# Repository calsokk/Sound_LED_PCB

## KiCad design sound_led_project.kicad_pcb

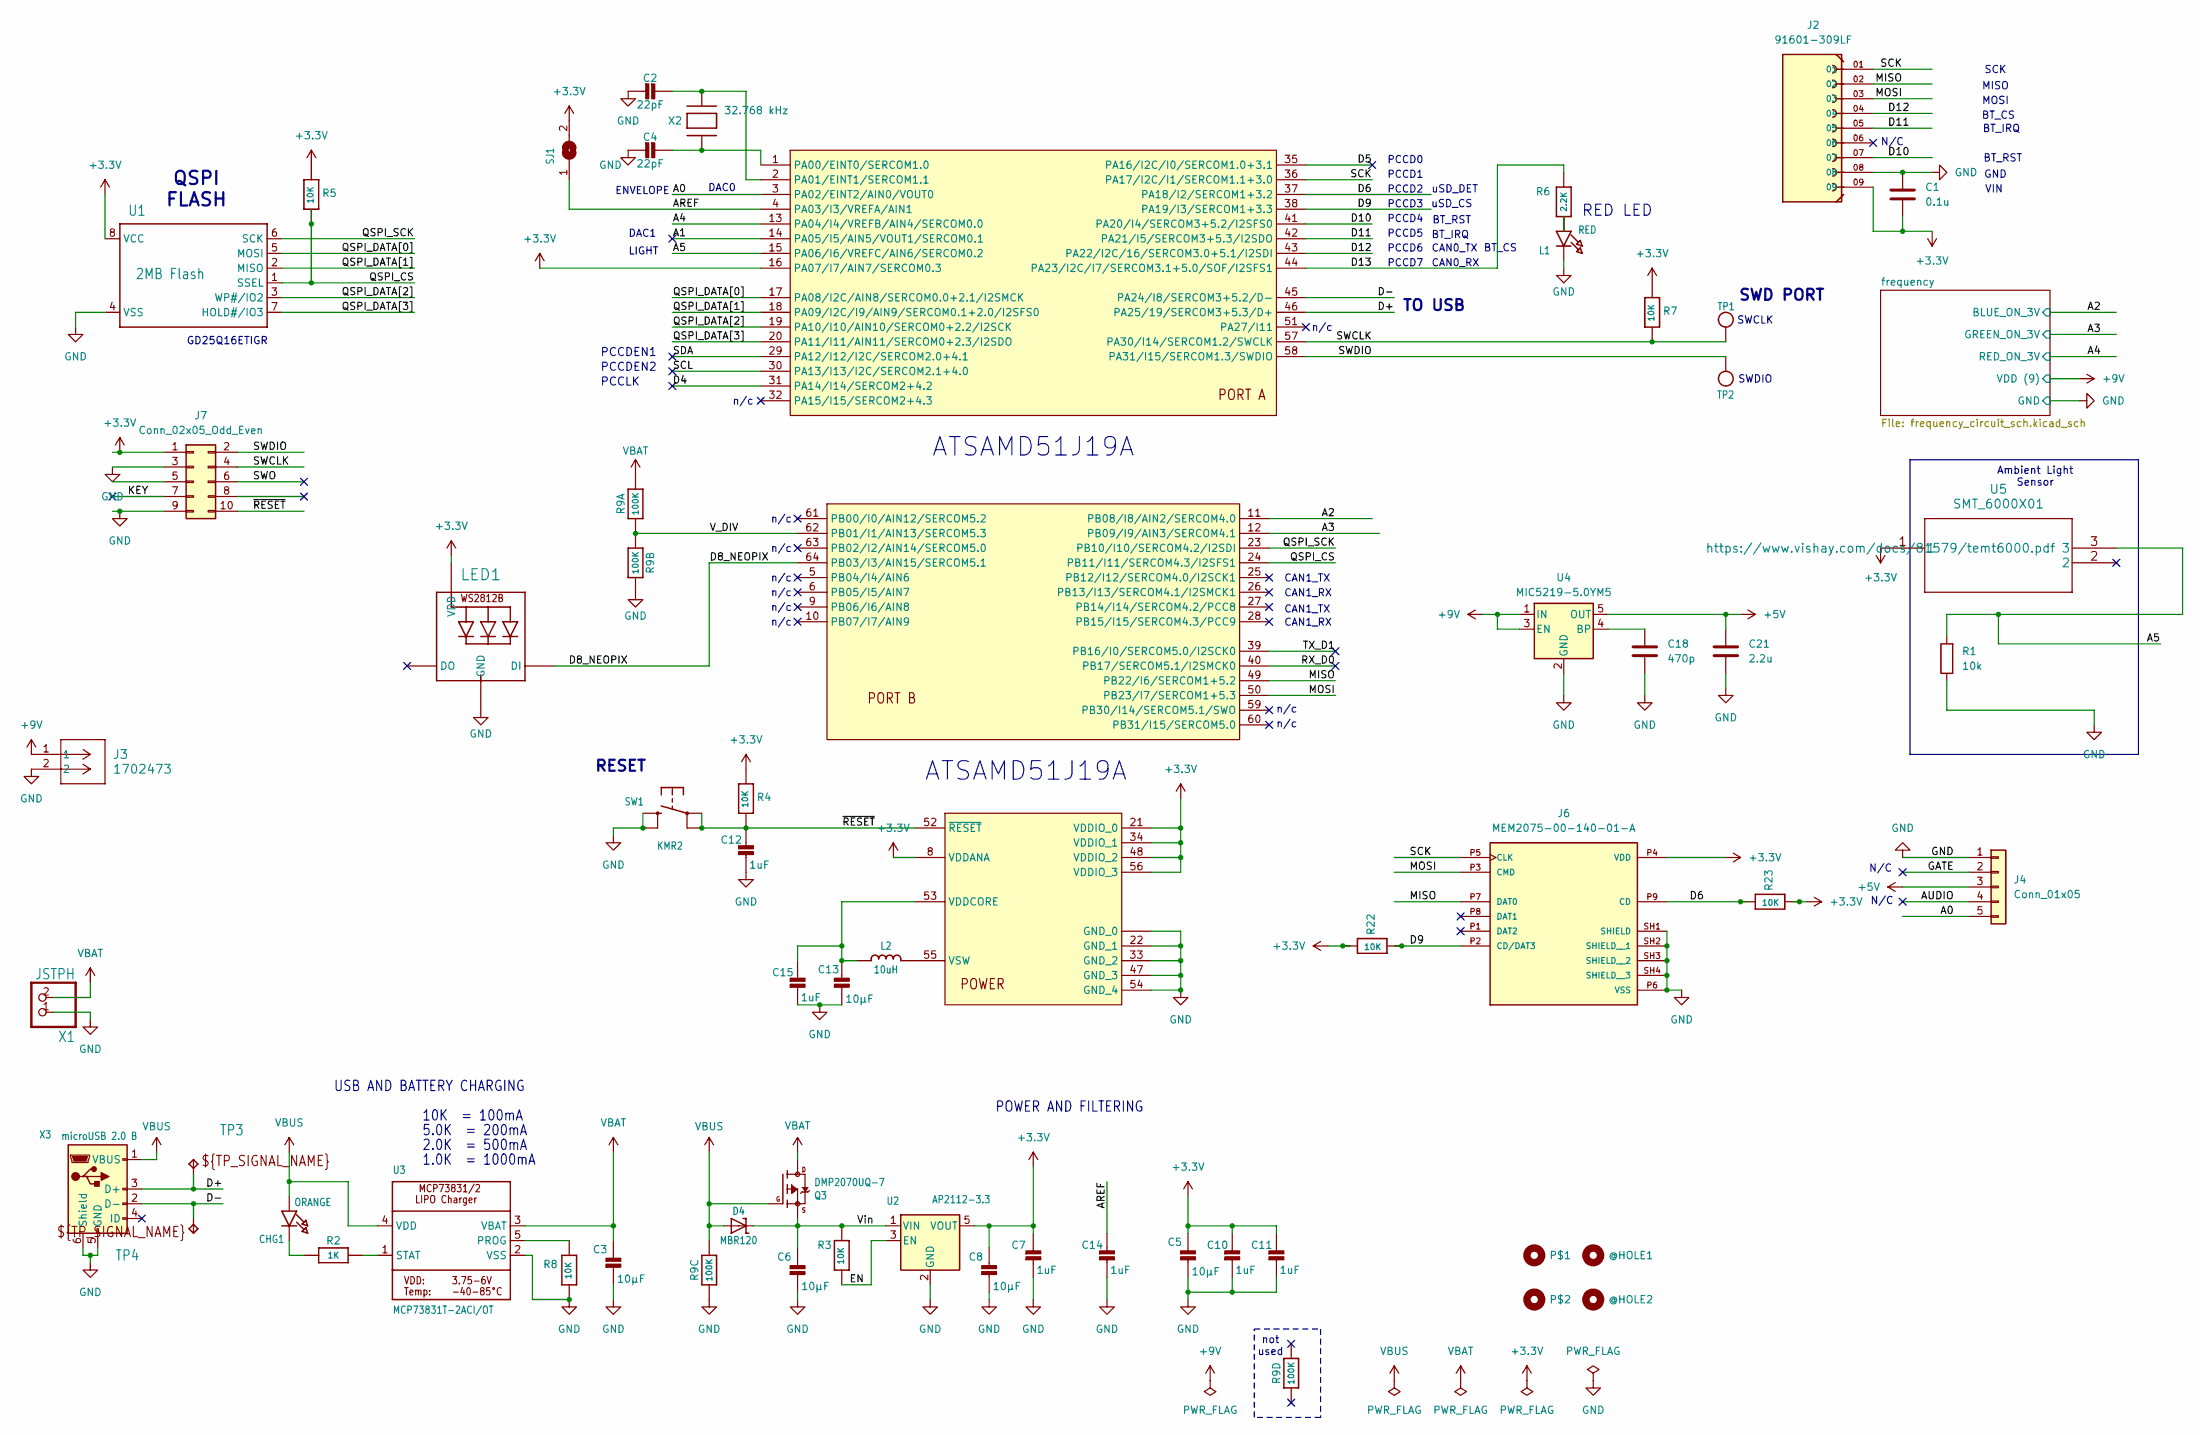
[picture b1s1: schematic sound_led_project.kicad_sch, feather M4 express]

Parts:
@HOLE1, @HOLE2: MountingHole; MountingHole_2.5mm
C1: 0.1u; C_0402_1005Metric_Pad0.74x0.62mm_HandSolder; Mfr P/N CL05B104KP5NNNC
C2, C4: 22pF; 0603-NO; Mfr P/N C0603C220K4GAC7867
C3, C5, C6, C8, C13: 10µF; 0805-NO; Mfr P/N CL21A106KOQNNNE
C7, C10, C11, C12, C14, C15: 1uF; C_0603_1608Metric_Pad1.08x0.95mm_HandSolder; Mfr P/N CC0603KRX7R7BB105
C18: 470p; C_0402_1005Metric_Pad0.74x0.62mm_HandSolder; Mfr P/N GRM155R71H471KA01D
C21: 2.2u; C_0201_0603Metric; Mfr P/N CL10A225KO8NNNC
CHG1: ORANGE; CHIPLED_0805_NOOUTLINE; Mfr P/N B1701UD--20D000414U1930
D4: MBR120; SOD-123; Mfr P/N MBR120LSFT1G
J2: 91601-309LF; AMPHENOL_91601-309LF; PARTREV AJ
J3: 1702473; Mfr P/N 1702473
J4: Conn_01x05; GCT_BG125-05-A-1-1-0440-N-D-TOP; Mfr P/N BG125-05-A-1-1-0440-N-D
J6: MEM2075-00-140-01-A; GCT_MEM2075-00-140-01-A; PARTREV A
J7: Conn_02x05_Odd_Even; AMPHENOL_20021521-00010T4LF; Mfr P/N 20021521-00010T4LF
L1: RED; CHIPLED_0805_NOOUTLINE; Mfr P/N LTST-S220KRKT
L2: 10uH; INDUCTOR_1007; Mfr P/N LSQEA251818T100K
LED1: WS2812B3535; LED3535; Mfr P/N SK6812MINI
P$1, P$2: MountingHole; MOUNTINGHOLE_2.5_PLATED
Q3: DMP2070UQ-7; SOT23-R; Mfr P/N DMP2070UQ-7
R1: 10k; R_0805_2012Metric_Pad1.20x1.40mm_HandSolder; Mfr P/N ERJ-U06D1002V
R2: 1K; 0603-NO; Mfr P/N MCT06030C1001FP500
R3, R4, R5, R7, R8, R22, R23: 10K; 0603-NO; Mfr P/N RNCP0603FTD10K0
R6: 2.2K; 0603-NO; Mfr P/N CRGH0603F2K2
R9: 100K; R_Array_Convex_4x0603; Mfr P/N CAY16-1003F4LF
SJ1: SOLDERJUMPERCLOSED; SOLDERJUMPER_CLOSEDWIRE
SW1: KMR2; BTN_KMR2_4.6X2.8; Mfr P/N KMR241NG ULC LFS
TP1, TP2: TESTPOINTROUND1.5MM; TESTPOINT_ROUND_1.5MM
TP3, TP4: B1,27_385
U1: 2MB Flash; SOIC-8_3.9x4.9mm_P1.27mm; Mfr P/N GD25Q16ETIGR
U2: AP2112-3.3; SOT-23-5; Mfr P/N AP2112K-3.3TRG1
U3: MCP73831T-2ACI/OT; SOT23-5; Mfr P/N MCP73831T-2ATI/OT
U4: MIC5219-5.0YM5; SOT-23-5; Mfr P/N MIC5219-5.0YM5-TR
U5: SMT_6000X01; TEMT6000X01; Mfr P/N TEMT6000X01
U$1: ATSAMD51J19A-AUT; TQFP-64_10x10mm_P0.5mm; Mfr P/N ATSAMD51J19A-AUT
X1: JSTPH; JST_PH_S2B-PH-SM4-TB_1x02-1MP_P2.00mm_Horizontal; Mfr P/N S2B-PH-SM4-TB
X2: 32.768 kHz; XTAL3215; Mfr P/N STDMUA17-32.768K
X3: microUSB 2.0 B; USB_Micro-B_Amphenol_10118194_Horizontal; Mfr P/N 10118194-0001LF

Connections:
+3.3V: C1.2, C5.1, C7.1, C8.1, C10.1, C11.1, J2.09, J6.P4 (VDD), J7.1, LED1.2 (VDD), R4.1, R5.1, R7.1, R22.1, R23.2, SJ1.2, U1.8 (VCC), U2.5 (VOUT), U5.1, U$1.8 (VDDANA), U$1.16 (PA07/I7/AIN7/SERCOM0.3), U$1.21 (VDDIO_0), U$1.34 (VDDIO_1), U$1.48 (VDDIO_2), U$1.56 (VDDIO_3)
+5V: C21.1, J4.3, U4.5 (OUT)
+9V: J3.1, U4.1 (IN), U4.3 (EN); also elsewhere on the board
/A0: J4.5, U$1.3 (PA02/EINT2/AIN0/VOUT0)
/A1: U$1.14 (PA05/I5/AIN5/VOUT1/SERCOM0.1)
/A2: U$1.11 (PB08/I8/AIN2/SERCOM4.0); also elsewhere on the board
/A3: U$1.12 (PB09/I9/AIN3/SERCOM4.1); also elsewhere on the board
/A4: U$1.13 (PA04/I4/VREFB/AIN4/SERCOM0.0); also elsewhere on the board
/A5: R1.2, U5.3, U$1.15 (PA06/I6/VREFC/AIN6/SERCOM0.2)
/AREF: C14.1, SJ1.1, U$1.4 (PA03/I3/VREFA/AIN1)
/AUDIO: J4.4
/D4: U$1.31 (PA14/I14/SERCOM2+4.2)
/D5: U$1.35 (PA16/I2C/I0/SERCOM1.0+3.1)
/D6: J6.P9 (CD), R23.1, U$1.37 (PA18/I2/SERCOM1+3.2)
/D8_NEOPIX: LED1.1 (DI), U$1.64 (PB03/I3/AIN15/SERCOM5.1)
/D9: J6.P2 (CD/DAT3), R22.2, U$1.38 (PA19/I3/SERCOM1+3.3)
/D10: J2.07, U$1.41 (PA20/I4/SERCOM3+5.2/I2SFS0)
/D11: J2.05, U$1.42 (PA21/I5/SERCOM3+5.3/I2SDO)
/D12: J2.04, U$1.43 (PA22/I2C/16/SERCOM3.0+5.1/I2SDI)
/D13: R6.1, U$1.44 (PA23/I2C/I7/SERCOM3.1+5.0/SOF/I2SFS1)
/D+: TP3.TP, U$1.46 (PA25/19/SERCOM3+5.3/D+), X3.3 (D+)
/D-: TP4.TP, U$1.45 (PA24/I8/SERCOM3+5.2/D-), X3.2 (D-)
/EN: R3.2, U2.3 (EN)
/GATE: J4.2
/KEY: J7.7
/MISO: J2.02, J6.P7 (DAT0), U$1.49 (PB22/I6/SERCOM1+5.2)
/MOSI: J2.03, J6.P3 (CMD), U$1.50 (PB23/I7/SERCOM1+5.3)
/QSPI_CS: R5.2, U1.1 (SSEL), U$1.24 (PB11/I11/SERCOM4.3/I2SFS1)
/QSPI_DATA[0]: U1.5 (MOSI), U$1.17 (PA08/I2C/AIN8/SERCOM0.0+2.1/I2SMCK)
/QSPI_DATA[1]: U1.2 (MISO), U$1.18 (PA09/I2C/I9/AIN9/SERCOM0.1+2.0/I2SFS0)
/QSPI_DATA[2]: U1.3 (WP#/IO2), U$1.19 (PA10/I10/AIN10/SERCOM0+2.2/I2SCK)
/QSPI_DATA[3]: U1.7 (HOLD#/IO3), U$1.20 (PA11/I11/AIN11/SERCOM0+2.3/I2SDO)
/QSPI_SCK: U1.6 (SCK), U$1.23 (PB10/I10/SERCOM4.2/I2SDI)
/RX_D0: U$1.40 (PB17/SERCOM5.1/I2SMCK0)
/SCK: J2.01, J6.P5 (CLK), U$1.36 (PA17/I2C/I1/SERCOM1.1+3.0)
/SCL: U$1.30 (PA13/I13/I2C/SERCOM2.1+4.0)
/SDA: U$1.29 (PA12/I12/I2C/SERCOM2.0+4.1)
/SWCLK: J7.4, R7.2, TP1.P$1, U$1.57 (PA30/I14/SERCOM1.2/SWCLK)
/SWDIO: J7.2, TP2.P$1, U$1.58 (PA31/I15/SERCOM1.3/SWDIO)
/SWO: J7.6
/TX_D1: U$1.39 (PB16/I0/SERCOM5.0/I2SCK0)
/V_DIV: R9.1, R9.2 (1), U$1.62 (PB01/I1/AIN13/SERCOM5.3)
/Vin: C6.1, D4.C, Q3.2 (S), R3.1, U2.1 (VIN)
/~RESET: C12.1, J7.10, R4.2, SW1.A, SW1.A' (P1), U$1.52 (~RESET)
GND: C1.1, C2.2, C3.2, C4.2, C5.2, C6.2, C7.2, C8.2, C10.2, C11.2, C12.2, C13.2, C14.2, C15.2, C18.2, C21.2, J2.08, J3.2, J4.1, J6.P6 (VSS), J6.SH1 (SHIELD), J6.SH2 (SHIELD__1), J6.SH3 (SHIELD__2), J6.SH4 (SHIELD__3), J7.3, J7.9, L1.C, LED1.4 (GND), R1.1, R8.2, R9.3 (1), R9.7 (2), SW1.B (S), SW1.B' (S1), U1.4 (VSS), U2.2 (GND), U3.2 (VSS), U4.2 (GND), U$1.7 (GND_0), U$1.22 (GND_1), U$1.33 (GND_2), U$1.47 (GND_3), U$1.54 (GND_4), X1.1, X3.5 (GND), X3.6 (Shield); also elsewhere on the board
unnamed: CHG1.C, R2.1
unnamed: L1.A, R6.2
unnamed: C13.1, C15.1, L2.P$1 (1), U$1.53 (VDDCORE)
unnamed: L2.P$2 (2), U$1.55 (VSW)
unnamed: R8.1, U3.5 (PROG)
unnamed: R2.2, U3.1 (STAT)
unnamed: C18.1, U4.4 (BP)
unnamed: C4.1, U$1.1 (PA00/EINT0/SERCOM1.0), X2.P$1
unnamed: C2.1, U$1.2 (PA01/EINT1/SERCOM1.1), X2.P$2
VBAT: C3.1, Q3.3 (D), R9.8 (2), U3.3 (VBAT), X1.2
VBUS: CHG1.A, D4.A, Q3.1 (G), R9.6 (2), U3.4 (VDD), X3.1 (VBUS)

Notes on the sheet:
n/c
MISO
SCK
SWCLK
ATSAMD51J19A
USB AND BATTERY CHARGING
PCCD6
Ambient Light Sensor
RED LED
DAC1
CAN0_TX
PCCLK
SWDIO
PCCD5
10K = 100mA
BT_RST
CAN1_TX
TO USB
N/C
PCCD3
5.0K = 200mA
uSD_CS
uSD_DET
PCCD2
GD25Q16ETIGR
1.0K = 1000mA
2.0K = 500mA
GND
BT_CS
PCCD1
CAN1_RX
DAC0
LIGHT
VIN
MOSI
CAN0_RX
PCCD0
ENVELOPE
PCCD7
QSPI FLASH

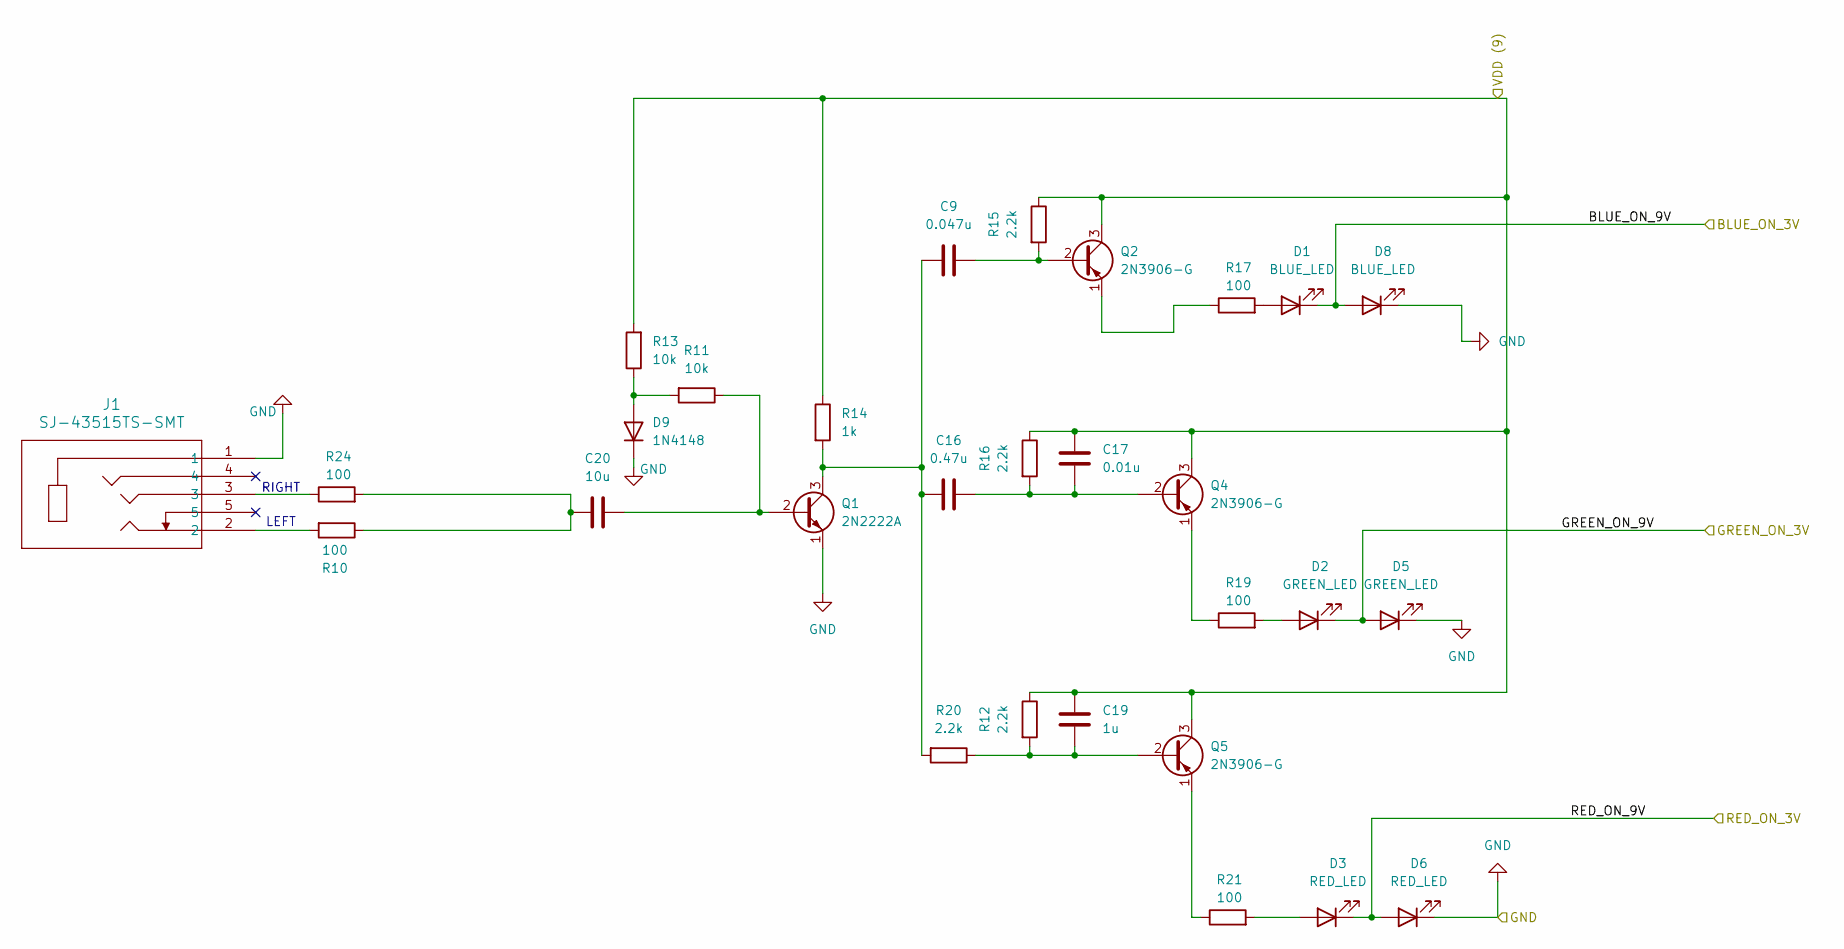
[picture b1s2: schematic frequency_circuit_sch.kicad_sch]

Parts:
C9: 0.047u; C_0402_1005Metric_Pad0.74x0.62mm_HandSolder; Mfr P/N GRM155R71E473KA88D
C16: 0.47u; C_0805_2012Metric_Pad1.18x1.45mm_HandSolder; Mfr P/N CL21B474KBFNNNG
C17: 0.01u; C_0201_0603Metric_Pad0.64x0.40mm_HandSolder; Mfr P/N GMD033R61A103KA01D
C19: 1u; C_0402_1005Metric_Pad0.74x0.62mm_HandSolder; Mfr P/N MAASL105CD7105MFCA01
C20: 10u; C_0805_2012Metric_Pad1.18x1.45mm_HandSolder; Mfr P/N CL21A106KOQNNNE
D1: BLUE_LED; LED_D5.0mm; Mfr P/N 151031SS06000
D2, D5: GREEN_LED; LED_D3.0mm; Mfr P/N 151031VS06000
D3, D6: RED_LED; LED_D3.0mm; Mfr P/N 151031SS06000
D8: BLUE_LED; LED_D5.0mm; Mfr P/N 151051BS04000
D9: 1N4148; D_DO-35_SOD27_P7.62mm_Horizontal; Mfr P/N 1N4148W-HG3_A-08
J1: SJ-43515TS-SMT; SJ-43515TS-SMT_CUD; Mfr P/N SJ-43515TS-SMT-TR
Q1: 2N2222A; TO92254P470H750-3; Mfr P/N 2N2222A
Q2, Q4, Q5: 2N3906-G; TO92127P470H495-3; Mfr P/N 2N3906-G
R10, R17, R19, R21, R24: 100; R_0603_1608Metric_Pad0.98x0.95mm_HandSolder; Mfr P/N Mfr. Part # ERJ-P03F1000V
R11, R13: 10k; R_0805_2012Metric_Pad1.20x1.40mm_HandSolder; Mfr P/N ERJ-U06D1002V
R12, R15, R16, R20: 2.2k; C_0201_0603Metric_Pad0.64x0.40mm_HandSolder; Mfr P/N ERJ-1GJF2201C
R14: 1k; R_0402_1005Metric_Pad0.72x0.64mm_HandSolder; Mfr P/N ERA-2ARC102X

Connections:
+9V: C17.1, C19.1, Q2.3 (C), Q4.3 (C), Q5.3 (C), R12.1, R13.2, R14.1, R15.1, R16.1; also elsewhere on the board
/A2: D1.1 (K), D8.2 (A); also elsewhere on the board
/A3: D2.1 (K), D5.2 (A); also elsewhere on the board
/A4: D3.1 (K), D6.2 (A); also elsewhere on the board
GND: D5.1 (K), D6.1 (K), D8.1 (K), D9.1 (K), J1.1, Q1.1 (E); also elsewhere on the board
unnamed: C20.1, R10.1, R24.2
unnamed: D1.2 (A), R17.2
unnamed: D2.2 (A), R19.2
unnamed: D3.2 (A), R21.2
unnamed: D9.2 (A), R11.2, R13.1
unnamed: J1.2, R10.2
unnamed: J1.3, R24.1
unnamed: C20.2, Q1.2 (B), R11.1
unnamed: C9.1, C16.1, Q1.3 (C), R14.2, R20.2
unnamed: C9.2, Q2.2 (B), R15.2
unnamed: Q2.1 (E), R17.1
unnamed: C16.2, C17.2, Q4.2 (B), R16.2
unnamed: Q4.1 (E), R19.1
unnamed: C19.2, Q5.2 (B), R12.2, R20.1
unnamed: Q5.1 (E), R21.1

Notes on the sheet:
LEFT
RIGHT

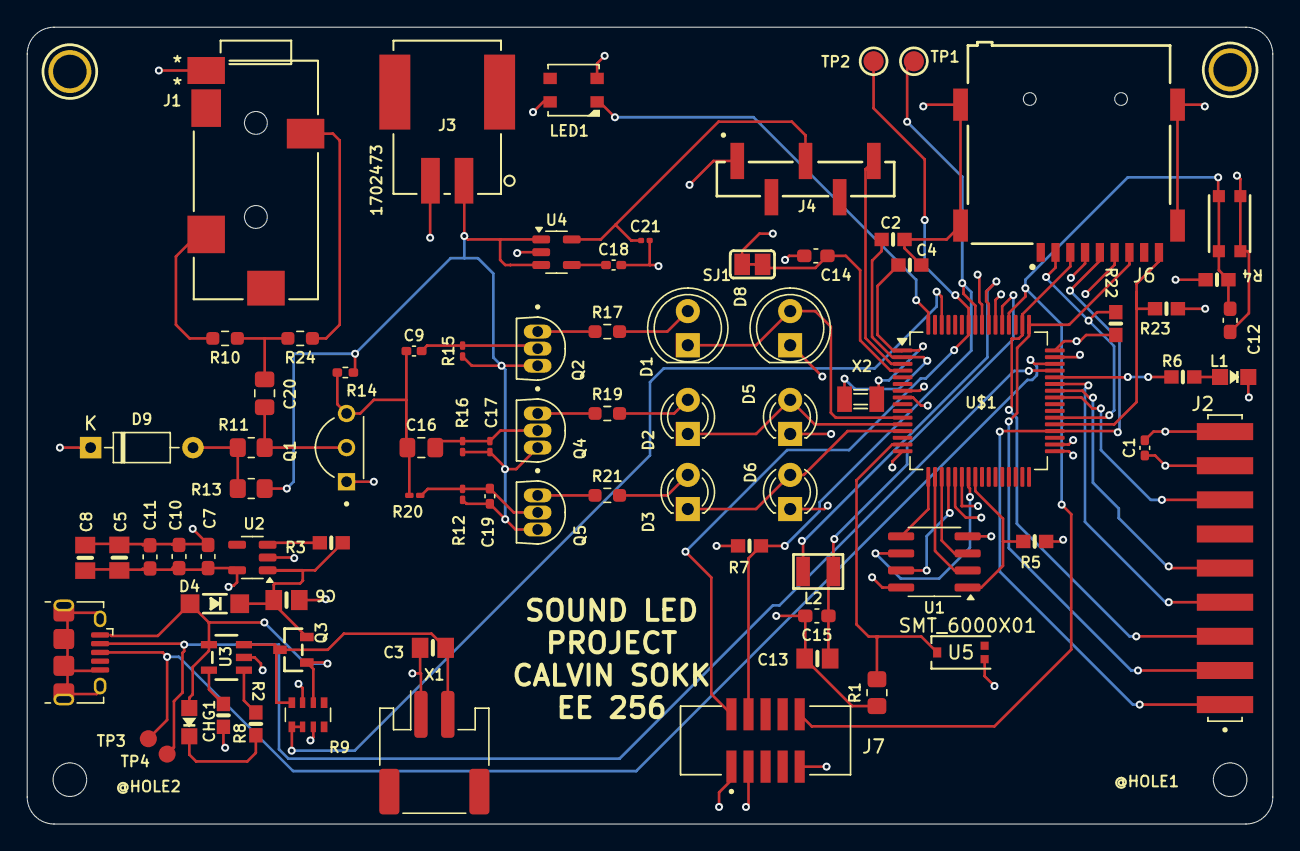
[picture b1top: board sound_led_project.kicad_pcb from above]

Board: 4 copper layers, 92.7 x 59.3 mm, 86 parts (0 on the bottom side), 60 nets.

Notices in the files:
parts and their libraries:
Copyright 2016 Accelerated Designs. All rights reserved.
